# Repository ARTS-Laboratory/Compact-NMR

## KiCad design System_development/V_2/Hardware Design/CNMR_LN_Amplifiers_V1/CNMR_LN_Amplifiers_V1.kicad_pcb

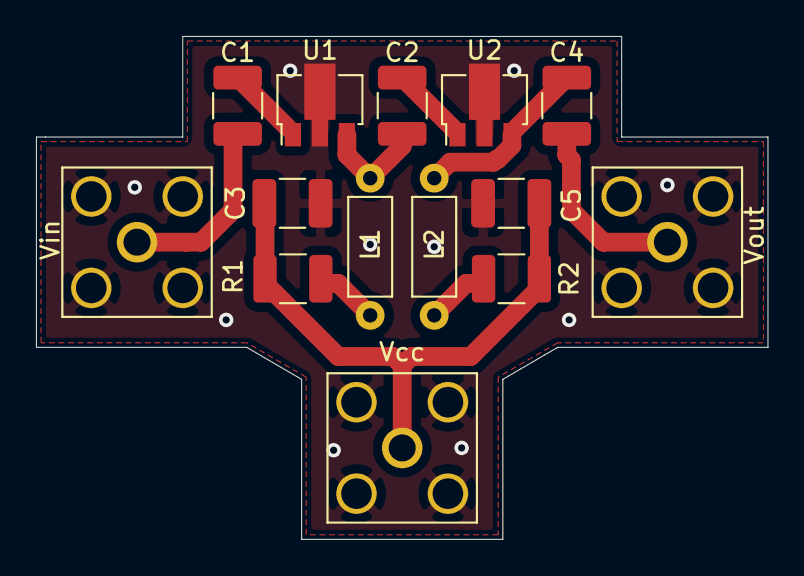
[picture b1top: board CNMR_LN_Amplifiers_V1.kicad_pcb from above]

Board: 2 copper layers, 40.6 x 27.9 mm, 14 parts (0 on the bottom side), 10 nets.

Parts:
C1, C2, C3, C4, C5: C; C_1210_3225Metric_Pad1.33x2.70mm_HandSolder
L1, L2: INDUCTOR; L_Axial_L5.3mm_D2.2mm_P7.62mm_Horizontal_Vishay_IM-1
R1, R2: R; R_1210_3225Metric_Pad1.30x2.65mm_HandSolder
U1, U2: GALI-S66; SOT-89-3
Vcc: Conn_Coaxial; SMA_Amphenol_132203-12_Horizontal
Vin: Conn_Coaxial; SMA_Amphenol_132203-12_Horizontal
Vout: Conn_Coaxial; SMA_Amphenol_132203-12_Horizontal

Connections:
GND: C3.1, C5.1, U1.2, U2.2, Vcc.2, Vin.2, Vout.2
unnamed: C1.1, U1.1
unnamed: C1.2, Vin.1
unnamed: C2.1, U2.1
unnamed: C2.2, L1.2, U1.3
unnamed: C3.2, C5.2, R1.1, R2.1, Vcc.1
unnamed: C4.1, Vout.1
unnamed: C4.2, L2.2, U2.3
unnamed: L1.1, R1.2
unnamed: L2.1, R2.2

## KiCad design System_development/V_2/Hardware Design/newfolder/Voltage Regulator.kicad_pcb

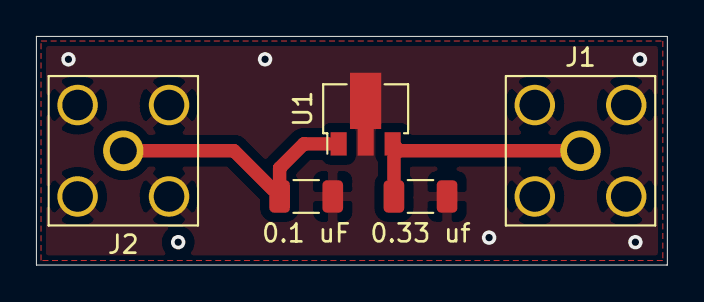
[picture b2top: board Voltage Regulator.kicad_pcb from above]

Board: 2 copper layers, 35.1 x 12.7 mm, 5 parts (0 on the bottom side), 3 nets.

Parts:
0.1 uF: 0.1uF; C_1206_3216Metric
0.33 uf: 0.33uf; C_1206_3216Metric
J1, J2: Conn_Coaxial; SMA_Amphenol_132203-12_Horizontal
U1: L78L12_SOT89; SOT-89-3

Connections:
GND1: 0.1 uF.2, 0.33 uf.2, J1.2, J2.2, U1.2
unnamed: 0.33 uf.1, J1.1, U1.3
unnamed: 0.1 uF.1, J2.1, U1.1

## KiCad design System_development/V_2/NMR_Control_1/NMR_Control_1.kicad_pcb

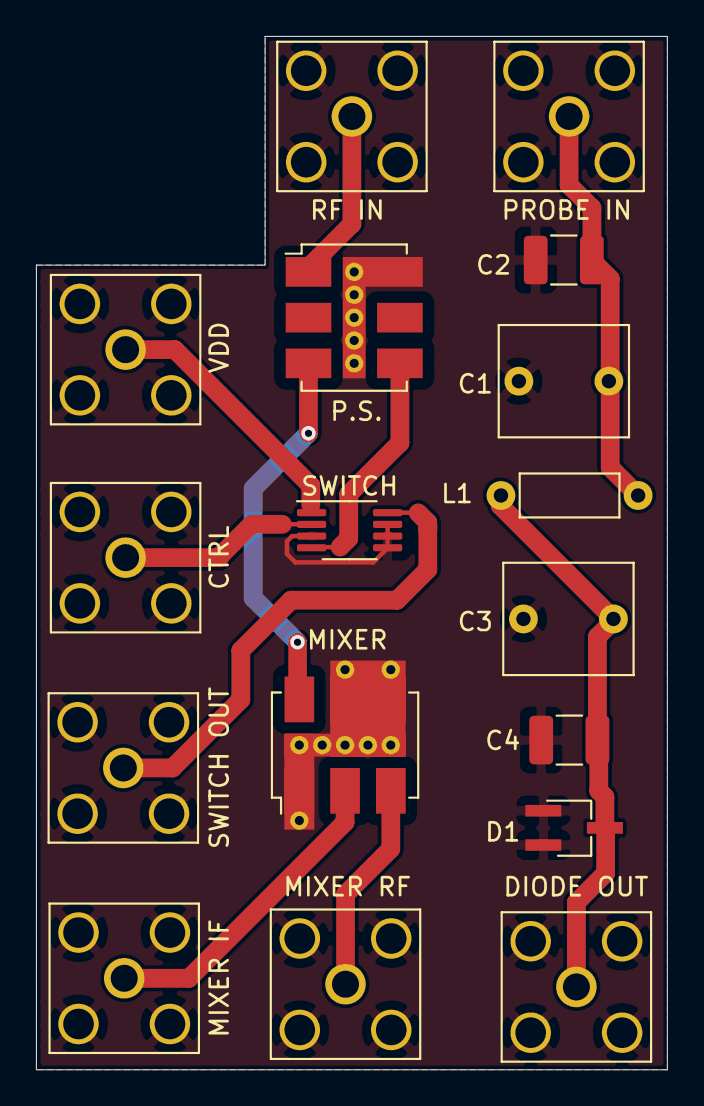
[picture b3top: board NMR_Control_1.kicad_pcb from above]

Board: 2 copper layers, 35.1 x 57.4 mm, 17 parts (0 on the bottom side), 11 nets.

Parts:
C1, C3: CTRIM; C_Rect_L7.0mm_W6.0mm_P5.00mm
C2, C4: C; C_1210_3225Metric_Pad1.33x2.70mm_HandSolder
CTRL: Conn_Coaxial; SMA_Amphenol_132203-12_Horizontal
D1: D_Schottky_x2_Serial_AKC; TSOT-23_HandSoldering
DIODE OUT: Conn_Coaxial; SMA_Amphenol_132203-12_Horizontal
L1: INDUCTOR; L_Axial_L5.3mm_D2.2mm_P7.62mm_Horizontal_Vishay_IM-1
MIXER: ADE-6; Mini-Circuits_CD542_LandPatternPL-052
MIXER IF: Conn_Coaxial; SMA_Amphenol_132203-12_Horizontal
MIXER RF: Conn_Coaxial; SMA_Amphenol_132203-12_Horizontal
P.S.: ADP-2-1W; Mini-Circuits_CD636_LandPatternPL-035
PROBE IN: Conn_Coaxial; SMA_Amphenol_132203-12_Horizontal
RF IN: Conn_Coaxial; SMA_Amphenol_132203-12_Horizontal
SWITCH: ADG901BRMZ; MSOP-8_3x3mm_P0.65mm
SWITCH OUT: Conn_Coaxial; SMA_Amphenol_132203-12_Horizontal
VDD: Conn_Coaxial; SMA_Amphenol_132203-12_Horizontal

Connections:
GND: C1.2, C2.2, C3.2, C4.2, CTRL.2, D1.1, D1.2, DIODE OUT.2, MIXER.1, MIXER.4, MIXER.5, MIXER IF.2, MIXER RF.2, P.S..6, PROBE IN.2, RF IN.2, SWITCH.3, SWITCH.5, SWITCH.6, SWITCH.7, SWITCH OUT.2, VDD.2
unnamed: C1.1, C2.1, L1.1, PROBE IN.1
unnamed: C3.1, C4.1, D1.3, DIODE OUT.1, L1.2
unnamed: P.S..1, RF IN.1
unnamed: CTRL.1, SWITCH.2
unnamed: MIXER.3, MIXER RF.1
unnamed: SWITCH.1, VDD.1
unnamed: MIXER.2, MIXER IF.1
unnamed: SWITCH.8, SWITCH OUT.1
unnamed: MIXER.6, P.S..3
unnamed: P.S..4, SWITCH.4

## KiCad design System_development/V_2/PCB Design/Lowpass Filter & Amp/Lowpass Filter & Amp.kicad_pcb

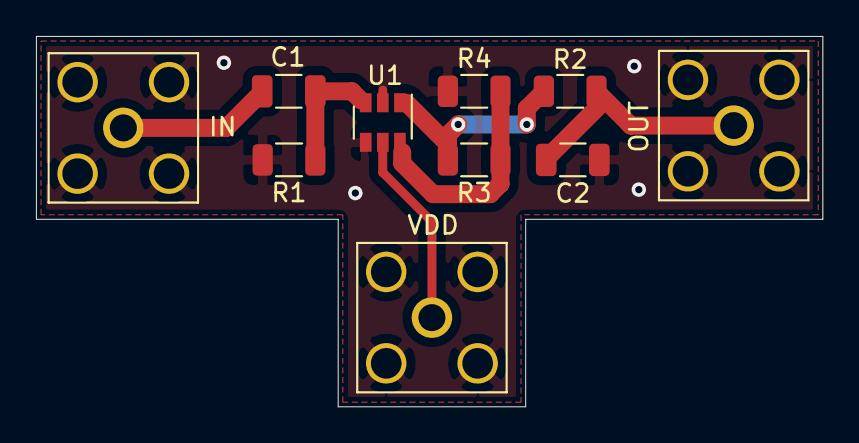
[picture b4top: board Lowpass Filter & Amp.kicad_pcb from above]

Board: 2 copper layers, 43.7 x 20.6 mm, 10 parts (0 on the bottom side), 7 nets.

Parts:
C1, C2: C; C_1206_3216Metric
IN: Conn_Coaxial; SMA_Amphenol_132203-12_Horizontal
OUT: Conn_Coaxial; SMA_Amphenol_132203-12_Horizontal
R1, R2, R3, R4: R; R_1206_3216Metric
U1: MAX4460; SOT-23-6
VDD: Conn_Coaxial; SMA_Amphenol_132203-12_Horizontal

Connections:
GND: C2.1, IN.2, OUT.2, R1.2, R4.1, U1.2, U1.4, VDD.2
unnamed: C1.1, R1.1, U1.3
unnamed: C1.2, IN.1
unnamed: C2.2, OUT.1, R2.1
unnamed: U1.5, VDD.1
unnamed: R2.2, R3.2, U1.1
unnamed: R3.1, R4.2, U1.6

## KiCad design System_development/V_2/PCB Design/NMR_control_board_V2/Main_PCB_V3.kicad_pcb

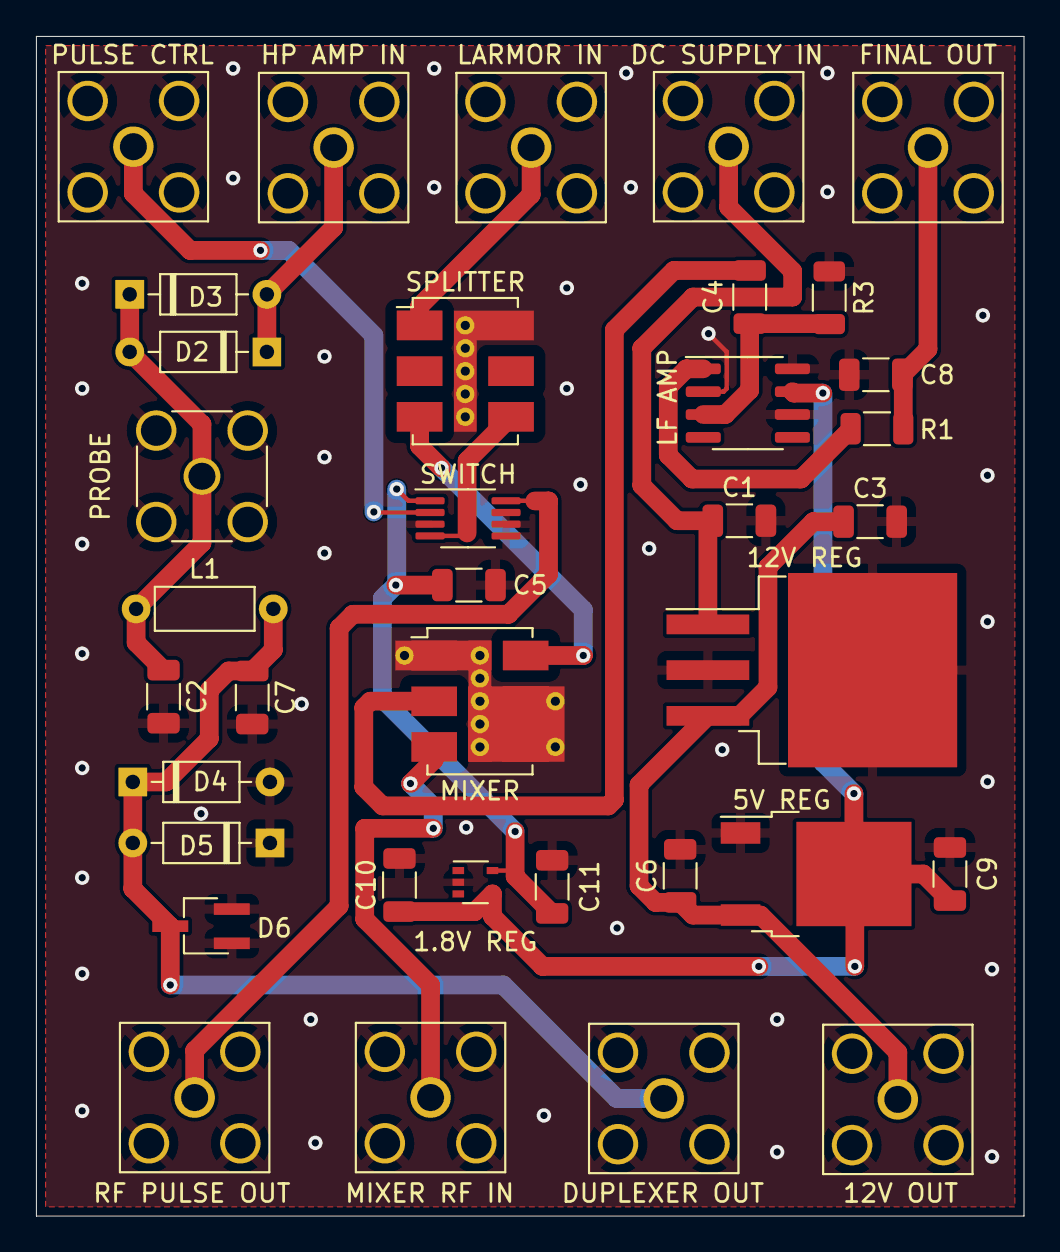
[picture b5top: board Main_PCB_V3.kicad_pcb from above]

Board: 2 copper layers, 54.9 x 65.5 mm, 36 parts (0 on the bottom side), 18 nets.

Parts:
1.8V REG: NCP715-1.8V; SOT-353_SC-70-5
5V REG: NCP1117-5.0_TO252; TO-252-2
12V OUT: Conn_Coaxial; SMA_Amphenol_132203-12_Horizontal
12V REG: LM7812_TO220; TO-263-3_TabPin2
C1: 0.33 uF; C_1206_3216Metric
C2, C4, C7, C8: C; C_1206_3216Metric
C3, C10, C11: 1 uF; C_1206_3216Metric
C5: 0.1 uF; C_1206_3216Metric
C6, C9: 10 uF; C_1206_3216Metric
D2, D3, D4, D5: 1N4148; D_DO-35_SOD27_P7.62mm_Horizontal
D6: D_Schottky_Dual_Series_AKC; TSOT-23_HandSoldering
DC SUPPLY IN: Conn_Coaxial; SMA_Amphenol_132203-12_Horizontal
DUPLEXER OUT: Conn_Coaxial; SMA_Amphenol_132203-12_Horizontal
FINAL OUT: Conn_Coaxial; SMA_Amphenol_132203-12_Horizontal
HP AMP IN: Conn_Coaxial; SMA_Amphenol_132203-12_Horizontal
L1: INDUCTOR; L_Axial_L5.3mm_D2.2mm_P7.62mm_Horizontal_Vishay_IM-1
LARMOR IN: Conn_Coaxial; SMA_Amphenol_132203-12_Horizontal
LF AMP: MAX4462 (8-SOIC); SOIC-8_3.9x4.9mm_P1.27mm
MIXER: ADE-6; Mini-Circuits_CD542_LandPatternPL-052
MIXER RF IN: Conn_Coaxial; SMA_Amphenol_132203-12_Horizontal
PROBE: Conn_Coaxial; SMA_Amphenol_132291-12_Vertical
PULSE CTRL: Conn_Coaxial; SMA_Amphenol_132203-12_Horizontal
R1, R3: R; R_1206_3216Metric
RF PULSE OUT: Conn_Coaxial; SMA_Amphenol_132203-12_Horizontal
SPLITTER: ADP-2-1W; Mini-Circuits_CD636_LandPatternPL-035
SWITCH: ADG901BRMZ; MSOP-8_3x3mm_P0.65mm

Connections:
GND: 1.8V REG.2 (GND), 5V REG.1 (GND), 12V OUT.2 (Ext), 12V REG.2 (GND), C1.2, C2.2, C3.2, C5.1, C6.2, C7.2, C8.1, C9.2, C10.2, C11.2, D4.2 (A), D5.1 (K), D6.1 (A), D6.2 (K), DC SUPPLY IN.2 (Ext), DUPLEXER OUT.2 (Ext), FINAL OUT.2 (Ext), HP AMP IN.2 (Ext), LARMOR IN.2 (Ext), LF AMP.2 (Vss), LF AMP.6 (V-), LF AMP.8 (REF), MIXER.1 (GND), MIXER.4 (GND), MIXER.5 (GND), MIXER RF IN.2 (Ext), PROBE.2 (Ext), PULSE CTRL.2 (Ext), R3.2, RF PULSE OUT.2 (Ext), SPLITTER.6 (GND), SWITCH.3 (GND), SWITCH.5 (GND), SWITCH.6 (GND), SWITCH.7 (GND)
unnamed: 12V REG.1 (VI), C1.1, DC SUPPLY IN.1 (In)
unnamed: C2.1, D2.2 (A), D3.1 (K), L1.1, PROBE.1 (In)
unnamed: 5V REG.3 (VI), 12V OUT.1 (In), 12V REG.3 (VO), C3.1, C6.1
unnamed: C4.1, MIXER.2 (IF)
unnamed: C4.2, LF AMP.3 (V+), R3.1
unnamed: C7.1, D4.1 (K), D5.2 (A), D6.3 (common), DUPLEXER OUT.1 (In), L1.2
unnamed: C8.2, FINAL OUT.1 (In), R1.2
unnamed: 1.8V REG.4 (IN), 5V REG.2 (VO), C9.1, C10.1, LF AMP.7 (Vdd)
unnamed: 1.8V REG.5 (OUT), C5.2, C11.1, SWITCH.1 (VDD)
unnamed: D2.1 (K), D3.2 (A), HP AMP IN.1 (In)
unnamed: LARMOR IN.1 (In), SPLITTER.1 (SUM)
unnamed: PULSE CTRL.1 (In), SWITCH.2 (CTRL)
unnamed: MIXER.3 (RF), MIXER RF IN.1 (In)
unnamed: RF PULSE OUT.1 (In), SWITCH.8 (RF2)
unnamed: LF AMP.1 (OUT), R1.1
unnamed: MIXER.6 (LO), SPLITTER.3 (PORT1)
unnamed: SPLITTER.4 (PORT2), SWITCH.4 (RF1)

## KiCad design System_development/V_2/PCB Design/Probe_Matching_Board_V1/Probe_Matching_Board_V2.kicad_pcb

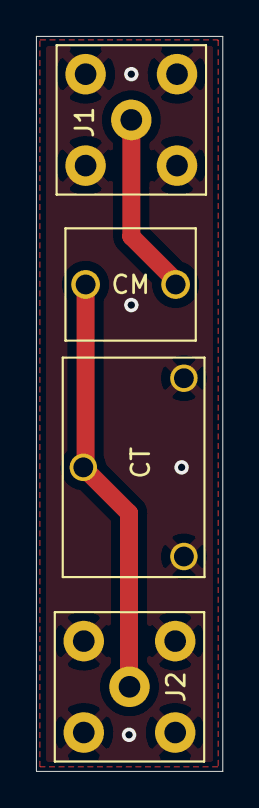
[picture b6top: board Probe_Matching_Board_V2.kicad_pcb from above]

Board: 2 copper layers, 10.4 x 40.8 mm, 4 parts (0 on the bottom side), 3 nets.

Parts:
CM: C_Variable; C_Rect_L7.0mm_W6.0mm_P5.00mm
CT: C_Trim_3_Leg; C_Trim_GZD10100
J1, J2: Conn_Coaxial; SMA_Amphenol_132203-12_Horizontal

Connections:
GND: CT.1, CT.2, J1.2, J2.2
unnamed: CM.1, CT.3, J2.1
unnamed: CM.2, J1.1

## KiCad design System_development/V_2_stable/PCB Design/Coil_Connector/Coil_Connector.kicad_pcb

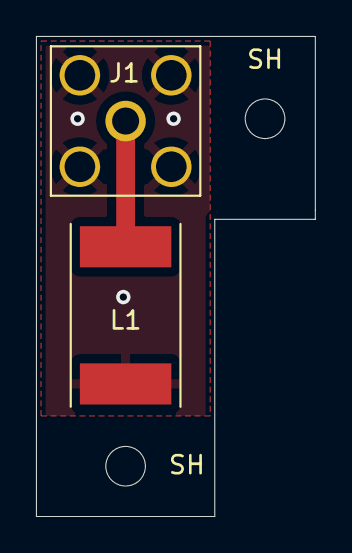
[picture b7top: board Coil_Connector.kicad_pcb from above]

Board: 2 copper layers, 15.5 x 26.7 mm, 4 parts (0 on the bottom side), 2 nets.

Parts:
J1: Conn_Coaxial; SMA_Amphenol_132203-12_Horizontal
L1: L; L_Coil
SH: MountingHole_2.2mm_M2
SH#2: MountingHole_2.2mm_M2

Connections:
GND: J1.2, L1.2
unnamed: J1.1, L1.1
